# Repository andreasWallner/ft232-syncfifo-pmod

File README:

**WIP**

# iceBreaker

References:
- https://github.com/icebreaker-fpga/icebreaker

# Arty-A7

References:
- https://digilent.com/reference/programmable-logic/arty-a7/reference-manual
- https://datasheet.octopart.com/XC7K160T-1FBG676I-Xilinx-datasheet-138898721.pdf#page=70
- https://www.xilinx.com/support/packagefiles/a7packages/xc7a35tcsg324pkg.txt
- https://www.xilinx.com/support/packagefiles/a7packages/xc7a100tcsg324pkg.txt

Pinout

    JC
    
    U12  IO_L20P_T3_A08_D24_14         3                  14    NA            NA                  HR        NA
    V12  IO_L20N_T3_A07_D23_14         3                  14    NA            NA                  HR        NA
    V10  IO_L21P_T3_DQS_14             3                  14    NA            NA                  HR        NA
    V11  IO_L21N_T3_DQS_A06_D22_14     3                  14    NA            NA                  HR        NA
    U14  IO_L22P_T3_A05_D21_14         3                  14    NA            NA                  HR        NA
    V14  IO_L22N_T3_A04_D20_14         3                  14    NA            NA                  HR        NA
    T13  IO_L23P_T3_A03_D19_14         3                  14    NA            NA                  HR        NA
    U13  IO_L23N_T3_A02_D18_14         3                  14    NA            NA                  HR        NA
    
    JB
    
    E15  IO_L11P_T1_SRCC_15            1                  15    NA            NA                  HR        NA
    E16  IO_L11N_T1_SRCC_15            1                  15    NA            NA                  HR        NA
    D15  IO_L12P_T1_MRCC_15            1                  15    NA            NA                  HR        NA
    C15  IO_L12N_T1_MRCC_15            1                  15    NA            NA                  HR        NA
    J17  IO_L23P_T3_FOE_B_15           3                  15    NA            NA                  HR        NA
    J18  IO_L23N_T3_FWE_B_15           3                  15    NA            NA                  HR        NA
    K15  IO_L24P_T3_RS1_15             3                  15    NA            NA                  HR        NA
    J15  IO_L24N_T3_RS0_15             3                  15    NA            NA                  HR        NA

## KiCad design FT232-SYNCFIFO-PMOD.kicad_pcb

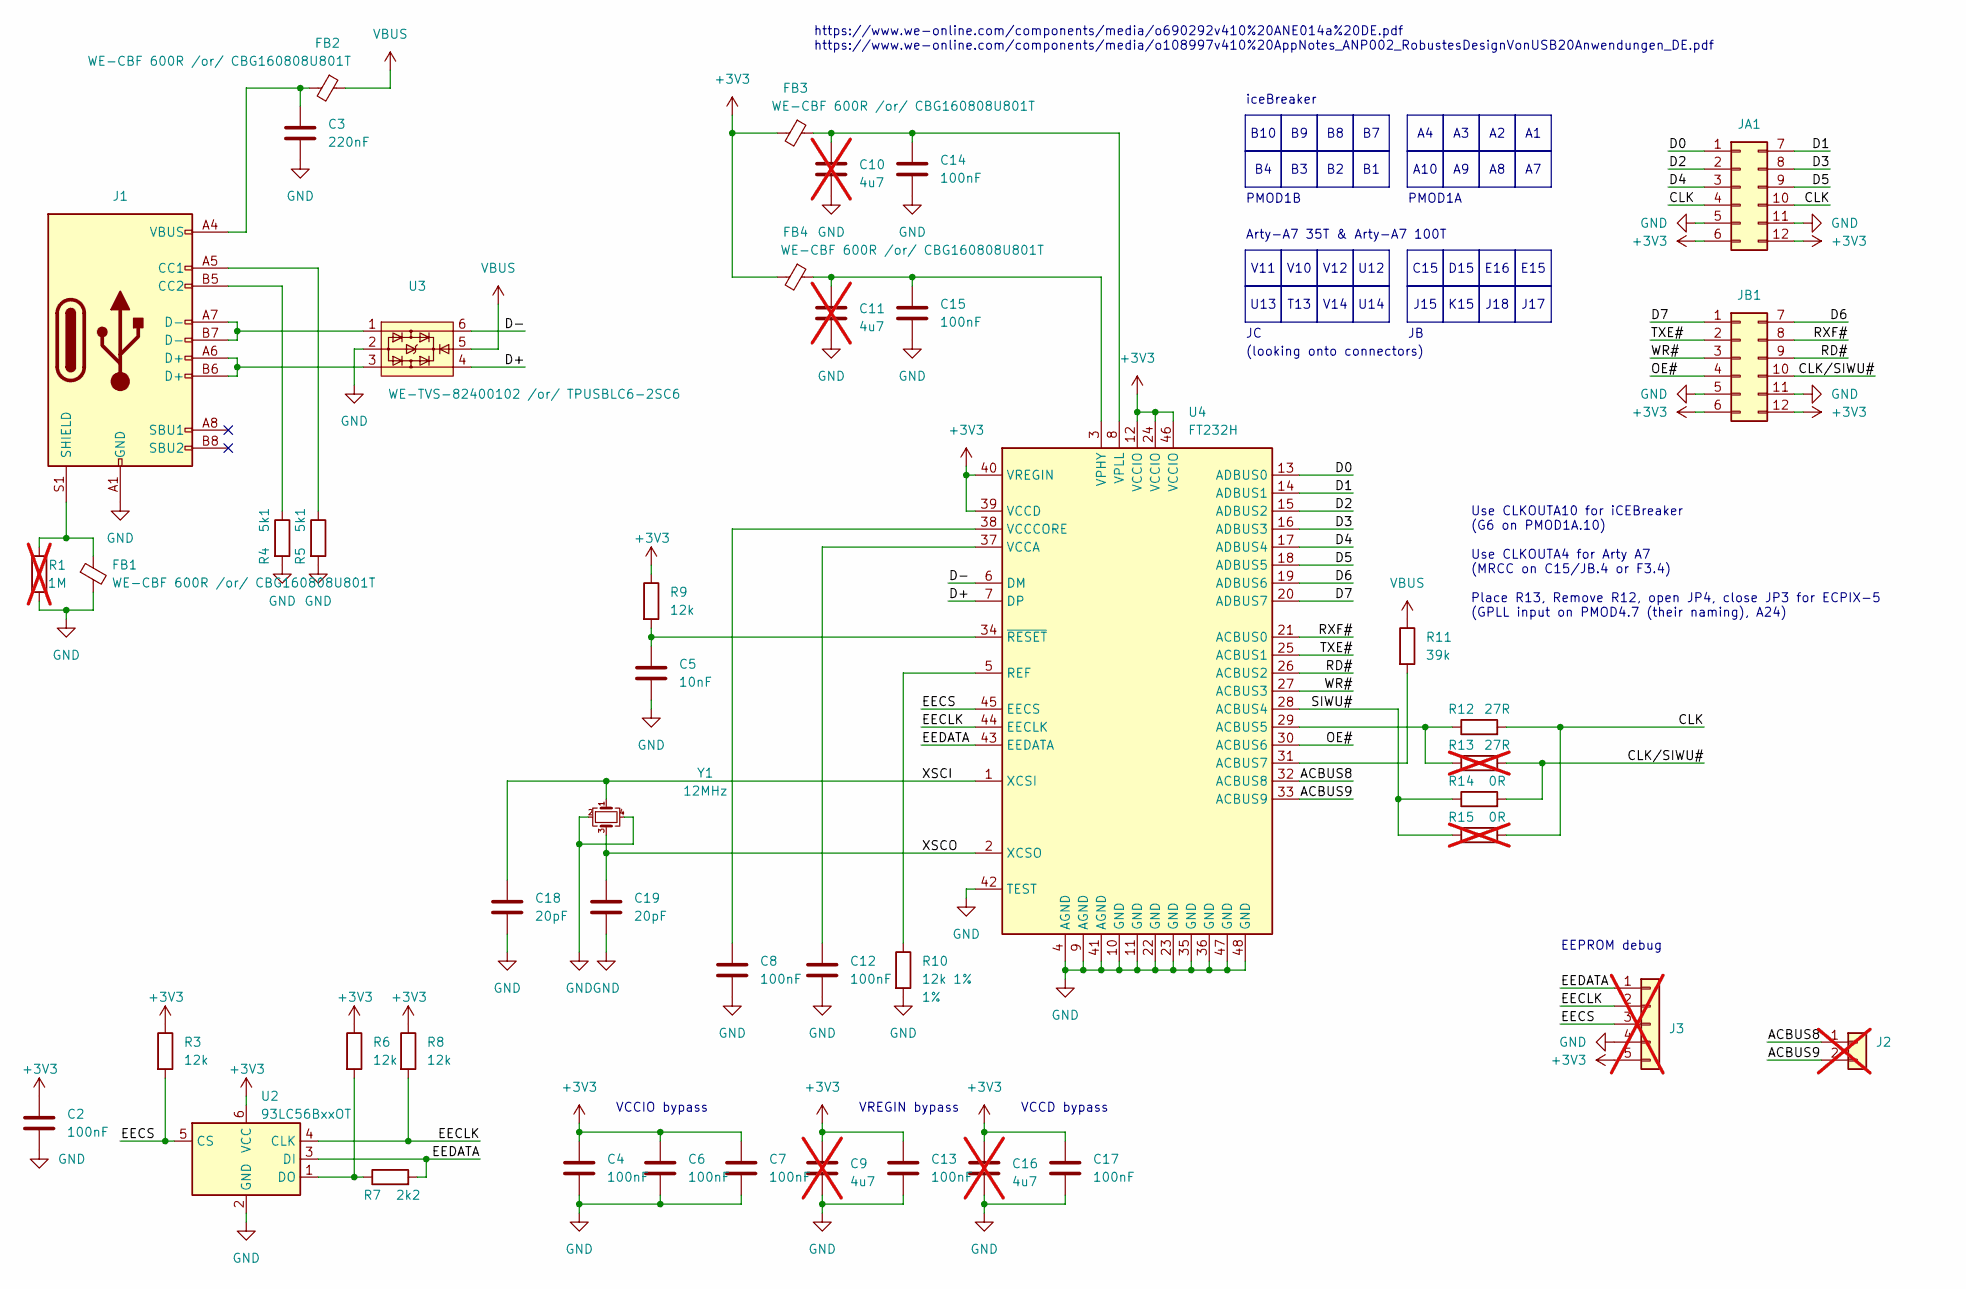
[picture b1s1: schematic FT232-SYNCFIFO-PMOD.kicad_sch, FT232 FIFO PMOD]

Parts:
C2, C4, C6, C7, C8, C12, C13, C14, C15, C17: 100nF; C_0402_1005Metric; LCSC C1525
C3: 220nF; C_0603_1608Metric; LCSC C16772
C5: 10nF; C_0402_1005Metric; LCSC C15195
C9, C10, C11, C16: 4u7; C_0402_1005Metric; not fitted
C18, C19: 20pF; C_0402_1005Metric; LCSC C1525
FB1, FB2, FB3, FB4: WE-CBF 600R /or/ CBG160808U801T; L_0603_1608Metric; LCSC C98500
J1: WR-COM USB 2.0 Type C Receptacle Horizontal SMT /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; wuerth_629722000214; LCSC C3001293
J2: dnp; PinHeader_1x02_P2.54mm_Vertical; not fitted
J3: Conn_01x05; PinHeader_1x05_P2.54mm_Vertical; not fitted
JA1: TE 825457-6; PinHeaderPMOD_2x06_P2.54mm_Horizontal; LCSC C60565
JB1: TE 825457-6; PinHeaderPMOD_2x06_P2.54mm_Horizontal; LCSC C60565
R1: 1M; R_0402_1005Metric; LCSC C102751; not fitted
R3, R6, R8, R9: 12k; R_0402_1005Metric; LCSC C25752
R4, R5: 5k1; R_0402_1005Metric; LCSC C409700
R7: 2k2; R_0402_1005Metric; LCSC C25879
R10: 12k 1%; R_0402_1005Metric; Tolerance 1%; LCSC C269386
R11: 39k; R_0402_1005Metric; LCSC C25752
R12: 27R; R_0402_1005Metric; LCSC C140174
R13: 27R; R_0402_1005Metric; LCSC C140174; not fitted
R14: 0R; R_0402_1005Metric; LCSC C279984
R15: 0R; R_0402_1005Metric; LCSC C279984; not fitted
U2: 93LC56BxxOT; SOT-23-6; LCSC C190271
U3: WE-TVS-82400102 /or/ TPUSBLC6-2SC6; SOT-23-6; LCSC C558442
U4: FT232H; QFN-48-1EP_8x8mm_P0.5mm_EP6.2x6.2mm; Farnell 1870925
Y1: 12MHz; Crystal_SMD_3225-4Pin_3.2x2.5mm_HandSoldering; LCSC C654952

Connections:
+3V3: C2.1, C4.1, C6.1, C7.1, C9.1, C13.1, C16.1, C17.1, FB3.2, FB4.2, J3.5, JA1.6, JA1.12, JB1.6, JB1.12, R3.1, R6.1, R8.1, R9.1, U2.6 (VCC), U4.12 (VCCIO), U4.24 (VCCIO), U4.39 (VCCD), U4.40 (VREGIN), U4.46 (VCCIO)
/ACBUS8: J2.1, U4.32 (ACBUS8)
/ACBUS9: J2.2, U4.33 (ACBUS9)
/CLK: JA1.4, JA1.10, R12.2, R15.2
/CLK/SIWU#: JB1.10, R13.1, R14.2
/D0: JA1.1, U4.13 (ADBUS0)
/D1: JA1.7, U4.14 (ADBUS1)
/D2: JA1.2, U4.15 (ADBUS2)
/D3: JA1.8, U4.16 (ADBUS3)
/D4: JA1.3, U4.17 (ADBUS4)
/D5: JA1.9, U4.18 (ADBUS5)
/D6: JB1.7, U4.19 (ADBUS6)
/D7: JB1.1, U4.20 (ADBUS7)
/D+: U3.4, U4.7 (DP)
/D-: U3.6, U4.6 (DM)
/EECLK: J3.2, R8.2, U2.4 (CLK), U4.44 (EECLK)
/EECS: J3.3, R3.2, U2.5 (CS), U4.45 (EECS)
/EEDATA: J3.1, R7.2, U2.3 (DI), U4.43 (EEDATA)
/OE#: JB1.4, U4.30 (ACBUS6)
/RD#: JB1.9, U4.26 (ACBUS2)
/RXF#: JB1.8, U4.21 (ACBUS0)
/SIWU#: R14.1, R15.1, U4.28 (ACBUS4)
/TXE#: JB1.2, U4.25 (ACBUS1)
/WR#: JB1.3, U4.27 (ACBUS3)
/XSCI: C18.1, U4.1 (XCSI), Y1.1
/XSCO: C19.1, U4.2 (XCSO), Y1.3
GND: C2.2, C3.2, C4.2, C5.2, C6.2, C7.2, C8.2, C9.2, C10.2, C11.2, C12.2, C13.2, C14.2, C15.2, C16.2, C17.2, C18.2, C19.2, FB1.2, J1.A1 (GND), J1.A12 (GND), J1.B1 (GND), J1.B12 (GND), J3.4, JA1.5, JA1.11, JB1.5, JB1.11, R1.2, R4.2, R5.2, R10.2, U2.2 (GND), U3.2, U4.4 (AGND), U4.9 (AGND), U4.10 (GND), U4.11 (GND), U4.22 (GND), U4.23 (GND), U4.35 (GND), U4.36 (GND), U4.41 (AGND), U4.42 (TEST), U4.47 (GND), U4.48 (GND), Y1.2, Y1.4
unnamed: C3.1, FB2.2, J1.A4 (VBUS), J1.A9 (VBUS), J1.B4 (VBUS), J1.B9 (VBUS)
unnamed: J1.A5 (CC1), R5.1
unnamed: J1.B5 (CC2), R4.1
unnamed: J1.A6 (D+), J1.B6 (D+), U3.3
unnamed: J1.A7 (D-), J1.B7 (D-), U3.1
unnamed: FB1.1, J1.S1 (SHIELD), R1.1
unnamed: R6.2, R7.1, U2.1 (DO)
unnamed: R12.1, R13.2, U4.29 (ACBUS5)
unnamed: R11.2, U4.31 (ACBUS7)
unnamed: R10.1, U4.5 (REF)
unnamed: C12.1, U4.37 (VCCA)
unnamed: C8.1, U4.38 (VCCCORE)
unnamed: C11.1, C15.1, FB4.1, U4.3 (VPHY)
unnamed: C10.1, C14.1, FB3.1, U4.8 (VPLL)
unnamed: C5.1, R9.2, U4.34 (~RESET)
VBUS: FB2.1, R11.1, U3.5

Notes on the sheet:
D15
E15
K15
V12
V11
V10
A10
V14
C15
U12
J15
U13
J18
J17
U14
E16
T13
B10
Use CLKOUTA10 for iCEBreaker (G6 on PMOD1A.10) Use CLKOUTA4 for Arty A7 (MRCC on C15/JB.4 or F3.4) Place R13, Remove R12, open JP4, close JP3 for ECPIX-5 (GPLL input on PMOD4.7 (their naming), A24)
https://www.we-online.com/components/media/o690292v410%20ANE014a%20DE.pdf https://www.we-online.com/components/media/o108997v410%20AppNotes_ANP002_RobustesDesignVonUSB20Anwendungen_DE.pdf
VCCD bypass
VCCIO bypass
iceBreaker
(looking onto connectors)
PMOD1A
VREGIN bypass
PMOD1B
Arty-A7 35T & Arty-A7 100T
EEPROM debug

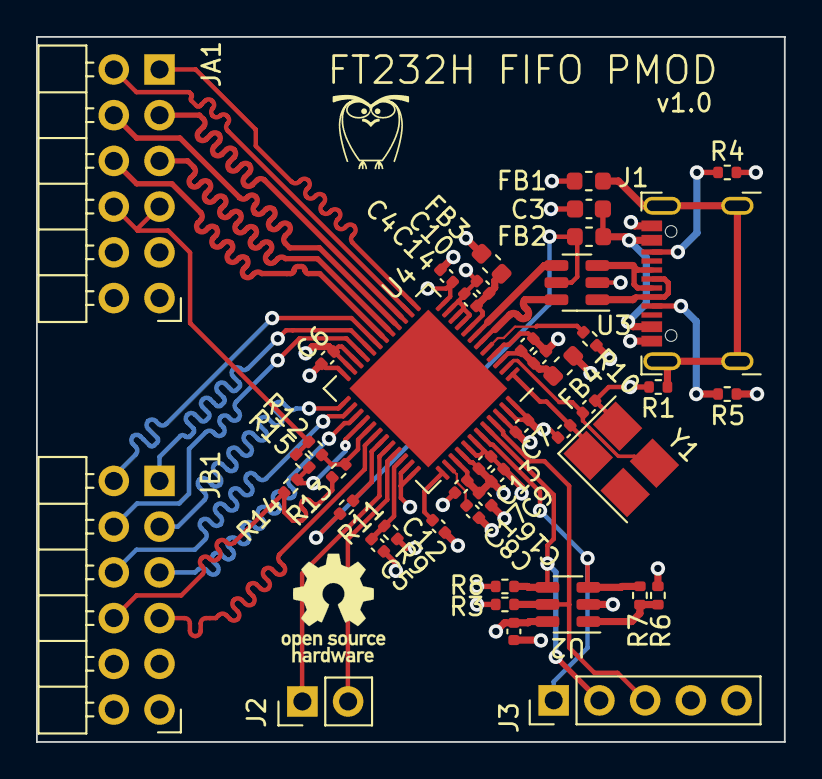
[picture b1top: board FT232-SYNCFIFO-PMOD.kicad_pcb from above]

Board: 4 copper layers, 41.5 x 39.2 mm, 45 parts (0 on the bottom side), 43 nets.
